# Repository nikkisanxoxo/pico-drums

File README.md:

## untested! ##

# pico-drums
Sample-player for Eurorack with RP2350/Pico2

# Developement is still in progress

# Pico Drum Module

A CircuitPython-based drum module with WAV sample playback, pitch shifting,
a low-pass filter, and a full ADSR envelope, all controlled via 8
potentiometers. Each module is a single-voice (mono) drum sound - build
several to form a full kit (kick, snare, hi-hat, ...).

## Hardware

| Component | Function |
|---|---|
| PCM5102A | I2S DAC for audio output |
| ADS7828 | 8-channel I2C ADC for the potentiometers |
| Trigger input | digital input, e.g. from a piezo/pad with external threshold circuitry |
| Button | trigger sample (short press) / switch sample (long press) |
| Board | Raspberry Pi Pico 2 (RP2350) |

### Pinout

| Pin | Function |
|---|---|
| GP0 | I2C SDA (ADS7828) |
| GP1 | I2C SCL (ADS7828) |
| GP14 | Trigger input (pull-down, rising edge = hit) |
| GP15 | Button (pull-up, switches to GND) |
| GP16 | I2S bit clock (PCM5102A BCK) |
| GP17 | I2S word select (PCM5102A LRCK) |
| GP18 | I2S data (PCM5102A DIN) |

The ADS7828 address is `0x48` (default address, ADDR pins tied to GND).

## Software requirements

- **CircuitPython 9.2.5 or newer** (the `audiodelays.PitchShift` module used
  for pitch shifting was only introduced in 9.2.5)
- No extra libraries required - everything used is part of the CircuitPython
  firmware

## File layout on the board

```
CIRCUITPY/
├── code.py            (or main.py)
└── samples/
    ├── sample_00.wav
    ├── sample_01.wav
    ├── sample_02.wav
    ├── ...
    └── sample_15.wav
```

Samples live in the `samples/` folder at the root of the CIRCUITPY drive and
are simply copied over via drag & drop.

### Sample file requirements

- Format: standard PCM WAV (mono or stereo - both are supported directly,
  since playback is streamed rather than loaded into RAM)
- Sample rate: should match `SAMPLE_RATE` in the code (44100 Hz by default)
- Length: effectively unlimited, only constrained by available flash storage
- File names exactly `sample_00.wav` through `sample_15.wav` (two digits,
  zero-padded) - adjust `NUM_SAMPLES` in the code if you have fewer

## Usage

### Trigger input (GP14)

A rising edge triggers the currently loaded sample using the current
potentiometer settings. A short lockout (3 ms) prevents multiple triggers
from piezo bounce.

### Button (GP15)

| Press duration | Action |
|---|---|
| short (< 1 s) | on release, triggers the current sample with the current pot settings (same as the trigger input) |
| long (>= 1 s) | switches to the next sample as soon as the threshold is reached (while still held down) |

### Potentiometers (ADS7828 channels)

| Channel | Function | Range |
|---|---|---|
| 0 | Volume | 0.0 - 1.0 |
| 1 | Tone (Pitch) | +/-1 octave, center = original sample pitch |
| 2 | Cutoff (filter) | 20 Hz - 20 kHz |
| 3 | Resonance (filter) | Q 0.5 - 10 |
| 4 | Attack | 5 ms - ~2 s |
| 5 | Decay | 5 ms - ~2 s |
| 6 | Sustain | 0.0 - 1.0 (level) |
| 7 | Release | 5 ms - ~2 s |

Pots are polled decoupled from the audio loop, every 20 ms
(`POT_UPDATE_INTERVAL`), since I2C transactions are comparatively slow.

## Architecture overview

- Samples are streamed directly from flash via `audiocore.WaveFile` through
  a single-voice `audiomixer.Mixer` - nothing is loaded into RAM, so there's
  no practical limit on sample length.
- A custom one-shot ADSR envelope drives the mixer voice's `level` each loop
  iteration (Attack -> Decay -> Release; there's no indefinite "sustain"
  hold, since a drum trigger never produces a note-off).
- Pitch is implemented via `audiodelays.PitchShift`, a real-time granular
  pitch-shift effect. It's only patched into the signal chain when the Tone
  pot deviates from its center position (outside `TONE_DEADZONE`) - when
  centered, the signal path skips it entirely (`Mixer -> Filter -> Output`)
  to avoid its window/overlap latency in the common case.
- A `audiofilters.Filter` (low-pass biquad) shapes the tone, controlled by
  the Cutoff/Resonance pots.
- Since each module only ever plays one voice, a new trigger immediately
  cuts off ("chokes") any hit still playing and restarts from the beginning.

## Latency tuning

The main knobs affecting trigger-to-sound latency:

- `BUFFER_SIZE` (default 512, ~11.6 ms at 44.1kHz) - the baseline latency of
  the whole audio chain (Mixer/PitchShift/Filter). Lower it for less
  latency, raise it if you hear dropouts/clicks.
- `window` / `overlap` in `audiodelays.PitchShift` (default 512/64) - only
  relevant while actually transposing (Tone pot off-center). Lower values
  reduce latency at the cost of more granular artifacts on strongly
  transposed sounds.
- `TONE_DEADZONE` - how close to center the Tone pot needs to be before
  `PitchShift` is bypassed entirely.

## Known limitations

- Switching samples (long button press) stops the currently playing voice,
  since both share the same mixer voice.
- `PitchShift` only switches in/out of the signal chain while the voice is
  idle, to avoid an audible click - moving the Tone pot in/out of its dead
  zone while a hit is playing won't take effect until the next trigger.
- `audiodelays.PitchShift` adds a small, constant latency whenever the Tone
  pot is off-center, due to its window/overlap-based processing.

## Troubleshooting

| Problem | Possible cause |
|---|---|
| No sound | Check I2S wiring (BCK/LRCK/DIN), confirm sample files exist, check the serial console for errors |
| `ImportError: no module named 'audiodelays'` | CircuitPython version is older than 9.2.5 - update the firmware |
| Pots seem swapped/wrong | Check ADS7828 wiring (SDA/SCL) and I2C address (`0x48`) |
| Sample won't load | Check filename/path (`/samples/sample_NN.wav`) |
| Audio clicks/dropouts | Increase `BUFFER_SIZE`, or increase `window`/`overlap` in `PitchShift` if it only happens while transposing |
| No serial output at all | Make sure the file is named `code.py` or `main.py`, connect the serial console before the board boots (or press Ctrl+D in the console to soft-reset) |

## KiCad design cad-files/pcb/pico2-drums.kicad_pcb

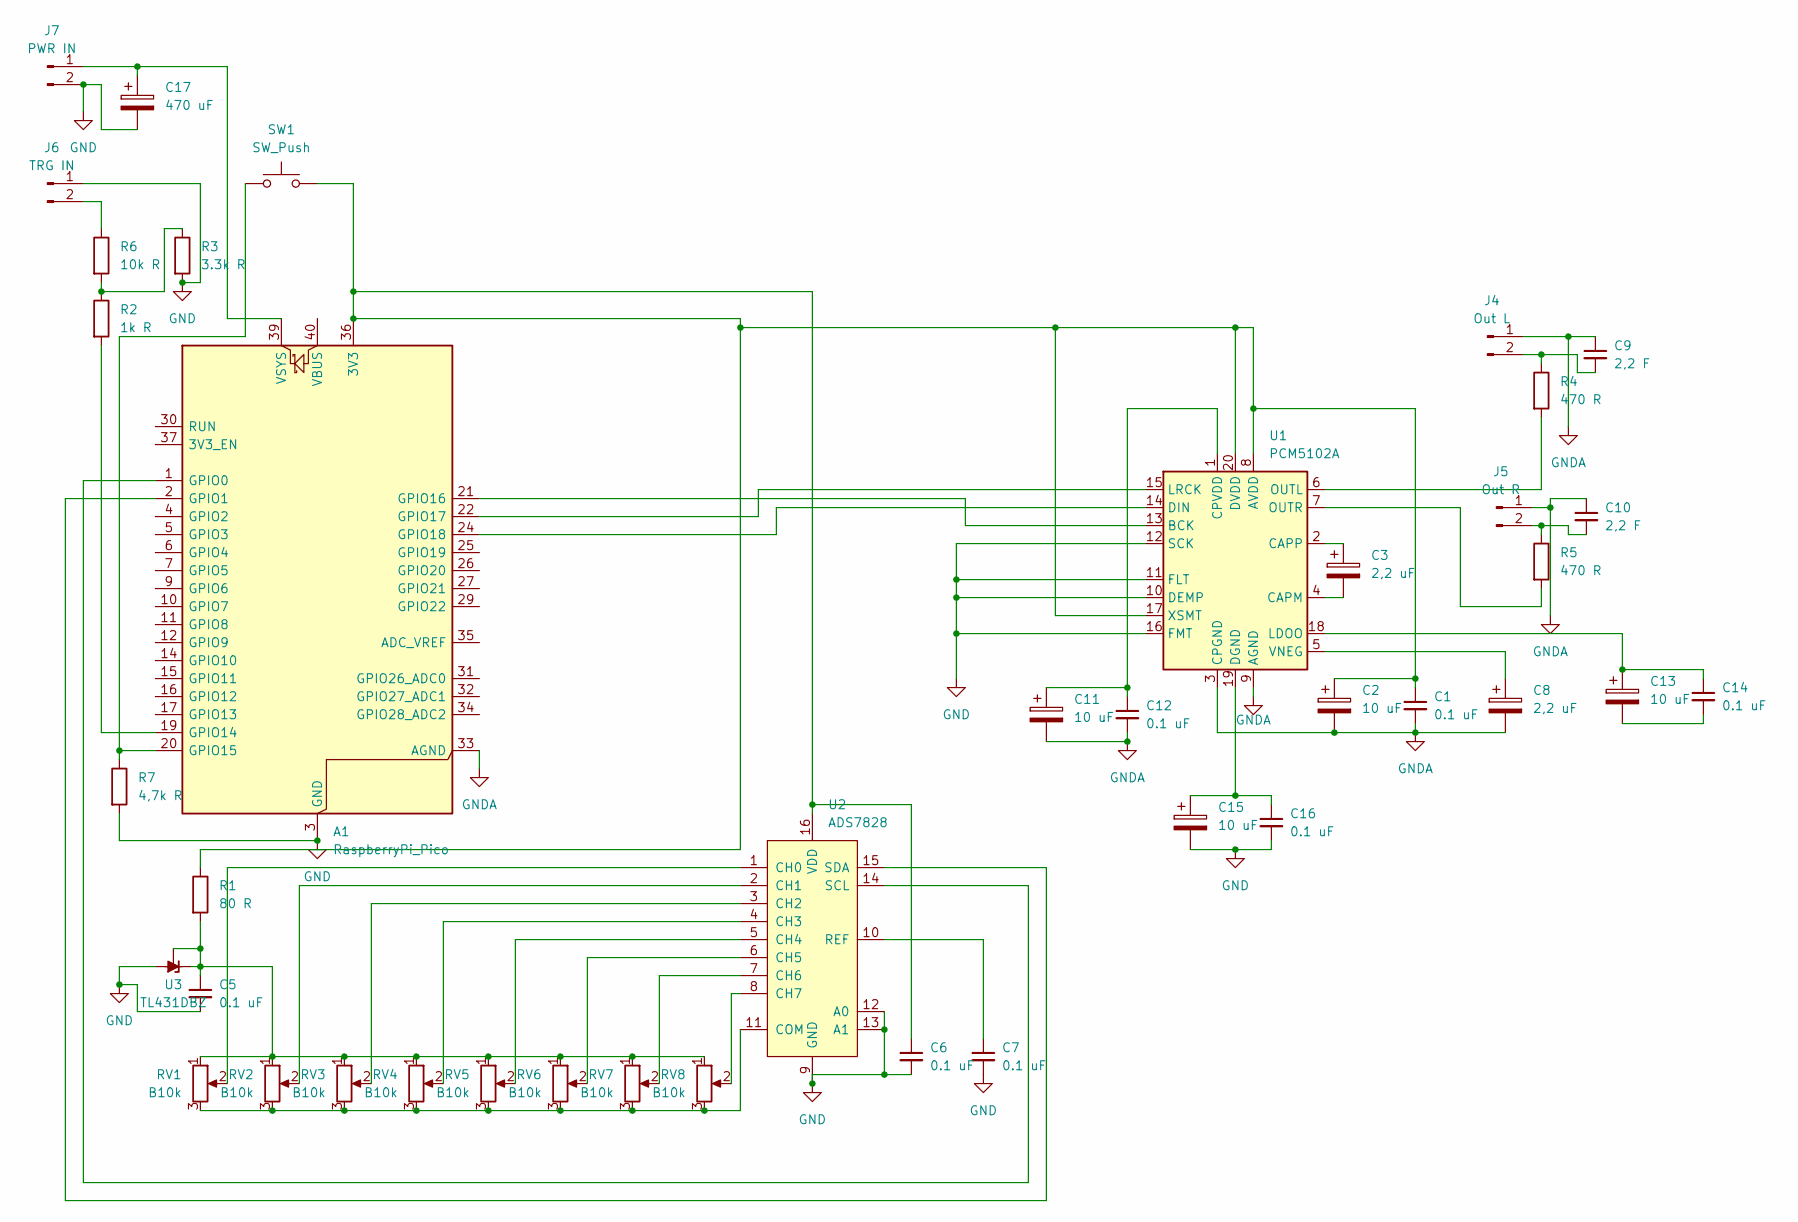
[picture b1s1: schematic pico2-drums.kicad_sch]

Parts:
A1: RaspberryPi_Pico; RaspberryPi_Pico_Common_Unspecified
C1, C5, C6, C7, C12, C14, C16: 0.1 uF; C_1206_3216Metric
C2, C11, C13, C15: 10 uF; CP_Elec_6.3x5.4
C3, C8: 2,2 uF; CP_Elec_6.3x5.4
C9, C10: 2,2 F; C_1206_3216Metric
C17: 470 uF; CP_Elec_8x10
J4: Out L; PinHeader_1x02_P2.54mm_Vertical
J5: Out R; PinHeader_1x02_P2.54mm_Vertical
J6: TRG IN; PinHeader_1x02_P2.54mm_Vertical
J7: PWR IN; PinHeader_1x02_P2.54mm_Vertical
R1: 80 R; R_1206_3216Metric
R2: 1k R; R_1206_3216Metric
R3: 3.3k R; R_1206_3216Metric
R4, R5: 470 R; R_1206_3216Metric
R6: 10k R; R_1206_3216Metric
R7: 4,7k R; R_1206_3216Metric
RV1, RV2, RV3, RV4, RV5, RV6, RV7, RV8: B10k; PinHeader_1x03_P2.54mm_Vertical
SW1: SW_Push; PinHeader_1x02_P2.54mm_Vertical
U1: PCM5102A; TSSOP-20_4.4x6.5mm_P0.65mm
U2: ADS7828; TSSOP-16_4.4x5mm_P0.65mm
U3: TL431DBZ; SOT-23

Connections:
GND: A1.3 (GND), A1.8 (GND), A1.13 (GND), A1.18 (GND), A1.23 (GND), A1.28 (GND), A1.38 (GND), C5.2, C6.2, C7.2, C15.2, C16.2, C17.2, J6.1, J7.2, R3.2, R7.2, U1.10 (DEMP), U1.11 (FLT), U1.12 (SCK), U1.16 (FMT), U2.9 (GND), U2.12 (A0), U2.13 (A1), U3.3 (A)
GNDA: A1.33 (AGND), C1.2, C2.2, C8.2, C9.1, C10.1, C11.2, C12.2, J4.1, J5.1, U1.3 (CPGND), U1.9 (AGND)
unnamed: A1.36 (3V3), C1.1, C2.1, C6.1, R1.1, SW1.2, U1.8 (AVDD), U1.17 (XSMT), U1.20 (DVDD), U2.16 (VDD)
unnamed: A1.1 (GPIO0), U2.14 (SCL)
unnamed: A1.2 (GPIO1), U2.15 (SDA)
unnamed: A1.19 (GPIO14), R2.2
unnamed: A1.20 (GPIO15), R7.1, SW1.1
unnamed: A1.21 (GPIO16), U1.13 (BCK)
unnamed: A1.22 (GPIO17), U1.15 (LRCK)
unnamed: A1.24 (GPIO18), U1.14 (DIN)
unnamed: A1.39 (VSYS), C17.1, J7.1
unnamed: C13.2, C14.2
unnamed: C9.2, J4.2, R4.1
unnamed: C10.2, J5.2, R5.1
unnamed: J6.2, R6.1
unnamed: R2.1, R3.1, R6.2
unnamed: C3.2, U1.4 (CAPM)
unnamed: C3.1, U1.2 (CAPP)
unnamed: C11.1, C12.1, U1.1 (CPVDD)
unnamed: C15.1, C16.1, U1.19 (DGND)
unnamed: C13.1, C14.1, U1.18 (LDOO)
unnamed: R4.2, U1.6 (OUTL)
unnamed: R5.2, U1.7 (OUTR)
unnamed: C8.1, U1.5 (VNEG)
unnamed: RV1.2, U2.1 (CH0)
unnamed: RV2.2, U2.2 (CH1)
unnamed: RV3.2, U2.3 (CH2)
unnamed: RV4.2, U2.4 (CH3)
unnamed: RV5.2, U2.5 (CH4)
unnamed: RV6.2, U2.6 (CH5)
unnamed: RV7.2, U2.7 (CH6)
unnamed: RV8.2, U2.8 (CH7)
unnamed: RV1.3, RV2.3, RV3.3, RV4.3, RV5.3, RV6.3, RV7.3, RV8.3, U2.11 (COM)
unnamed: C7.1, U2.10 (REF)
unnamed: C5.1, R1.2, RV1.1, RV2.1, RV3.1, RV4.1, RV5.1, RV6.1, RV7.1, RV8.1, U3.1 (K), U3.2 (REF)

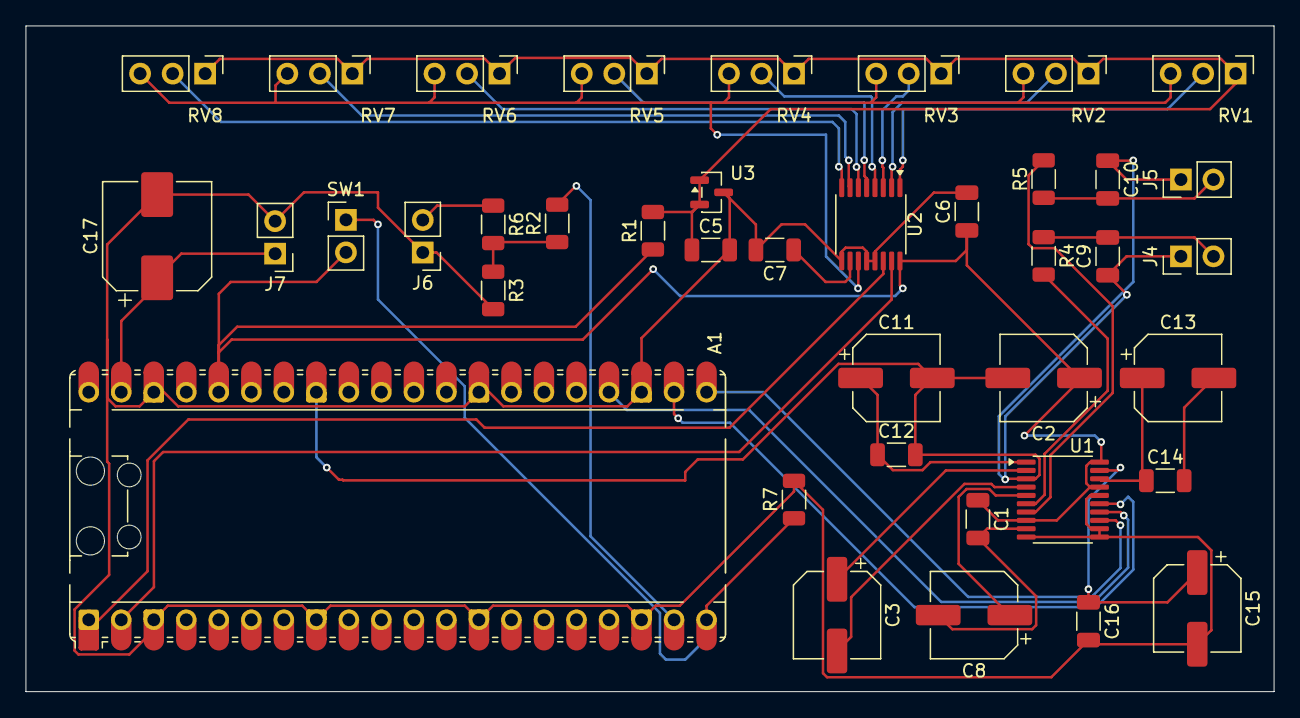
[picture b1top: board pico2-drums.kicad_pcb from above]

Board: 2 copper layers, 97.5 x 52.0 mm, 40 parts (0 on the bottom side), 35 nets.

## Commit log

2026-06-21 Delete lib directory
    library not needed
